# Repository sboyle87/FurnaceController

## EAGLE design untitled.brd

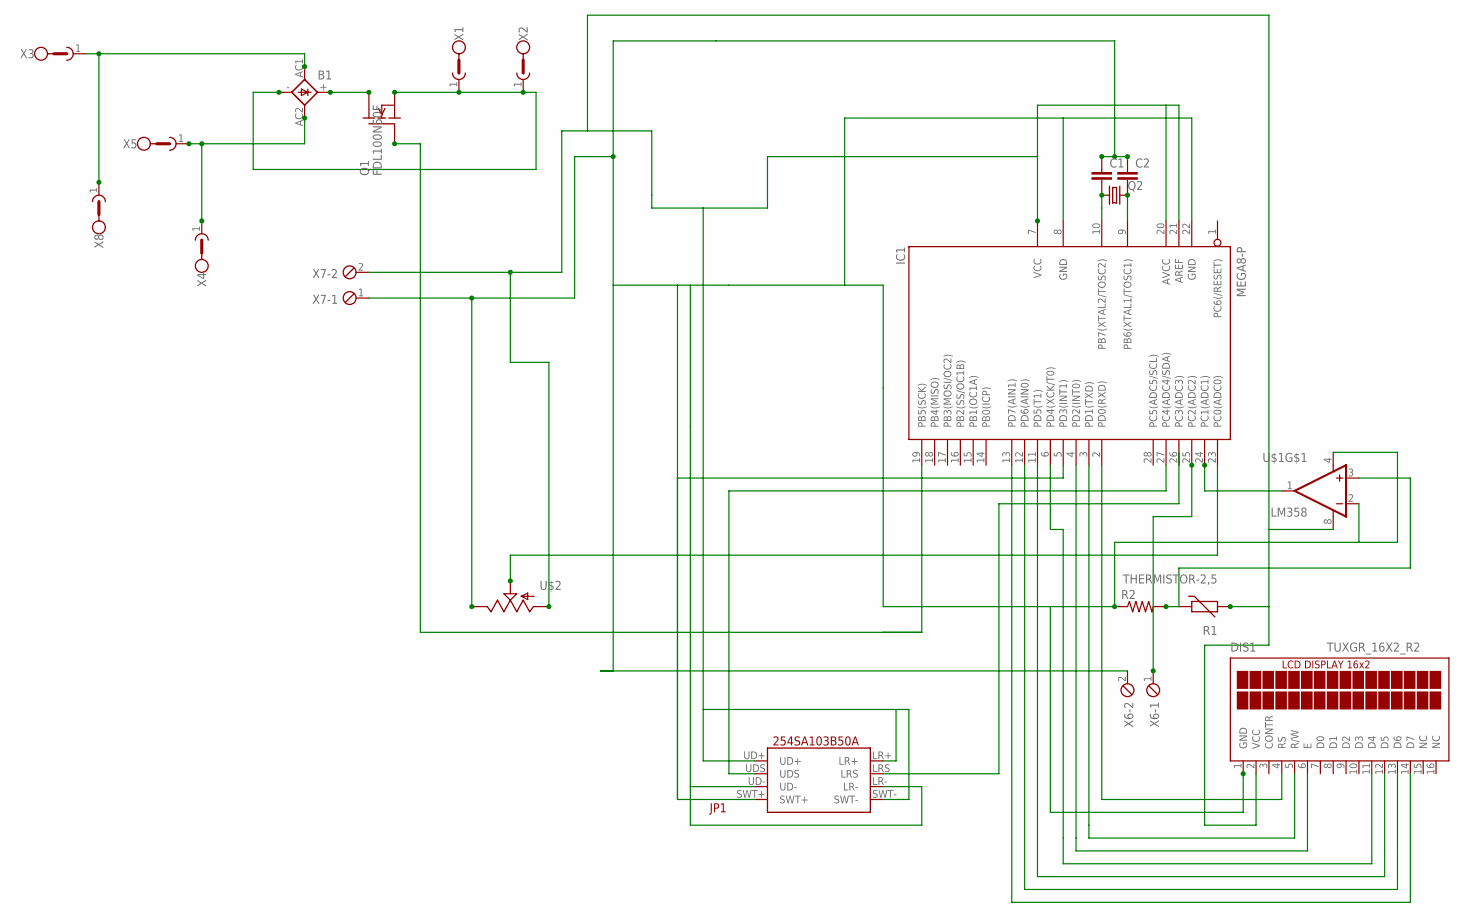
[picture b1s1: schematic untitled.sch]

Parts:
B1: FBM
C1, C2: CAPPTH1; CAP-PTH-5MM
DIS1: TUXGR_16X2_R2
IC1: MEGA8-P; DIL28-3
JP1: 254SA103B50A
Q1: FDL100N50F; TO264
Q2: CRYSTALHC49U-V; HC49U-V
R1: THERMISTOR-2,5; RS-2,5
R2: R-US_0207/7; 0207/7
U$1: LM358; DIP08
U$2: POT; ALPS_POT
X1, X2: GMSTBA2ZFKDS475; GMSTBA2
X3: 17805071780507; 1780507
X4, X5, X8: 17805071780507; 1780507; MPN 1757242
X6, X7: MPT2; 2POL254

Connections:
unnamed: IC1.10 (PB7(XTAL2/TOSC2)), Q2.1
unnamed: B1.+, Q1.2 (D)
unnamed: B1.-, Q1.3 (S), X1.1, X2.1
unnamed: IC1.19 (PB5(SCK)), Q1.1 (G)
unnamed: IC1.25 (PC2(ADC2)), X6.1
unnamed: IC1.9 (PB6(XTAL1/TOSC1)), Q2.2
unnamed: B1.AC2, X4.1, X5.1
unnamed: B1.AC1, X3.1, X8.1
unnamed: IC1.24 (PC1(ADC1)), U$1.1 (OUT)
unnamed: IC1.23 (PC0(ADC0)), U$2.P$2 (S)
unnamed: DIS1.2 (VCC), IC1.7 (VCC), IC1.20 (AVCC), IC1.21 (AREF), JP1.LR+, JP1.SWT-, JP1.UD+, R1.2, U$1.8 (V+), U$2.P$3 (A), X7.2
unnamed: DIS1.6 (E), IC1.4 (PD2(INT0))
unnamed: DIS1.11 (D4), IC1.6 (PD4(XCK/T0))
unnamed: R1.1, R2.2, U$1.3 (+IN)
unnamed: DIS1.12 (D5), IC1.11 (PD5(T1))
unnamed: DIS1.13 (D6), IC1.12 (PD6(AIN0))
unnamed: DIS1.4 (RS), IC1.2 (PD0(RXD))
unnamed: DIS1.5 (R/W), IC1.3 (PD1(TXD))
unnamed: DIS1.14 (D7), IC1.13 (PD7(AIN1))
unnamed: IC1.27 (PC4(ADC4/SDA)), JP1.UDS
unnamed: C1.1, C2.1, DIS1.1 (GND), IC1.5 (PD3(INT1)), IC1.8 (GND), IC1.22 (GND), JP1.LR-, JP1.SWT+, JP1.UD-, R2.1, U$1.2 (-IN), U$1.4 (V-), U$2.P$1 (E), X6.2, X7.1

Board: 2 copper layers, 20 parts (0 on the bottom side), 21 nets, no tracks yet.

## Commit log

2015-05-04 Initial

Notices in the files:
parts and their libraries:
SparkFun: Licensing: CC v3.0 Share-Alike You are welcome to use this library for commercial purposes.
